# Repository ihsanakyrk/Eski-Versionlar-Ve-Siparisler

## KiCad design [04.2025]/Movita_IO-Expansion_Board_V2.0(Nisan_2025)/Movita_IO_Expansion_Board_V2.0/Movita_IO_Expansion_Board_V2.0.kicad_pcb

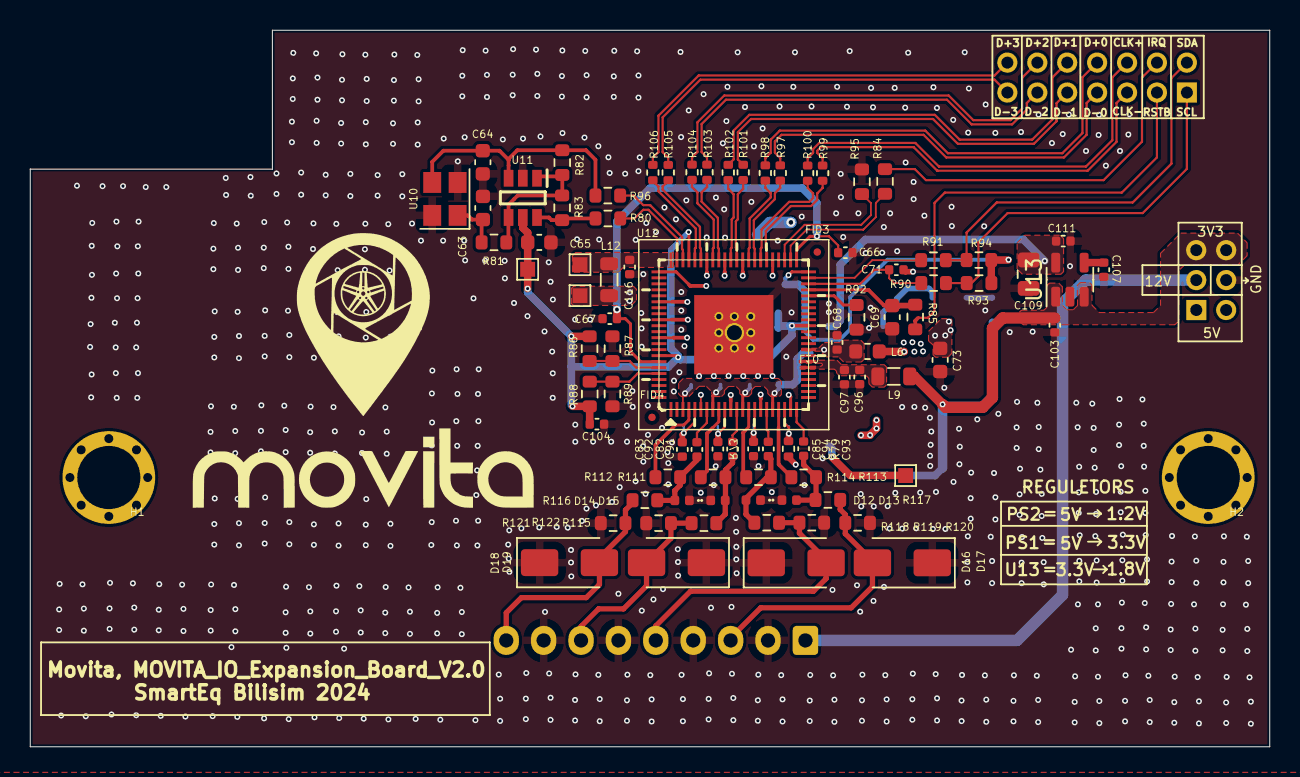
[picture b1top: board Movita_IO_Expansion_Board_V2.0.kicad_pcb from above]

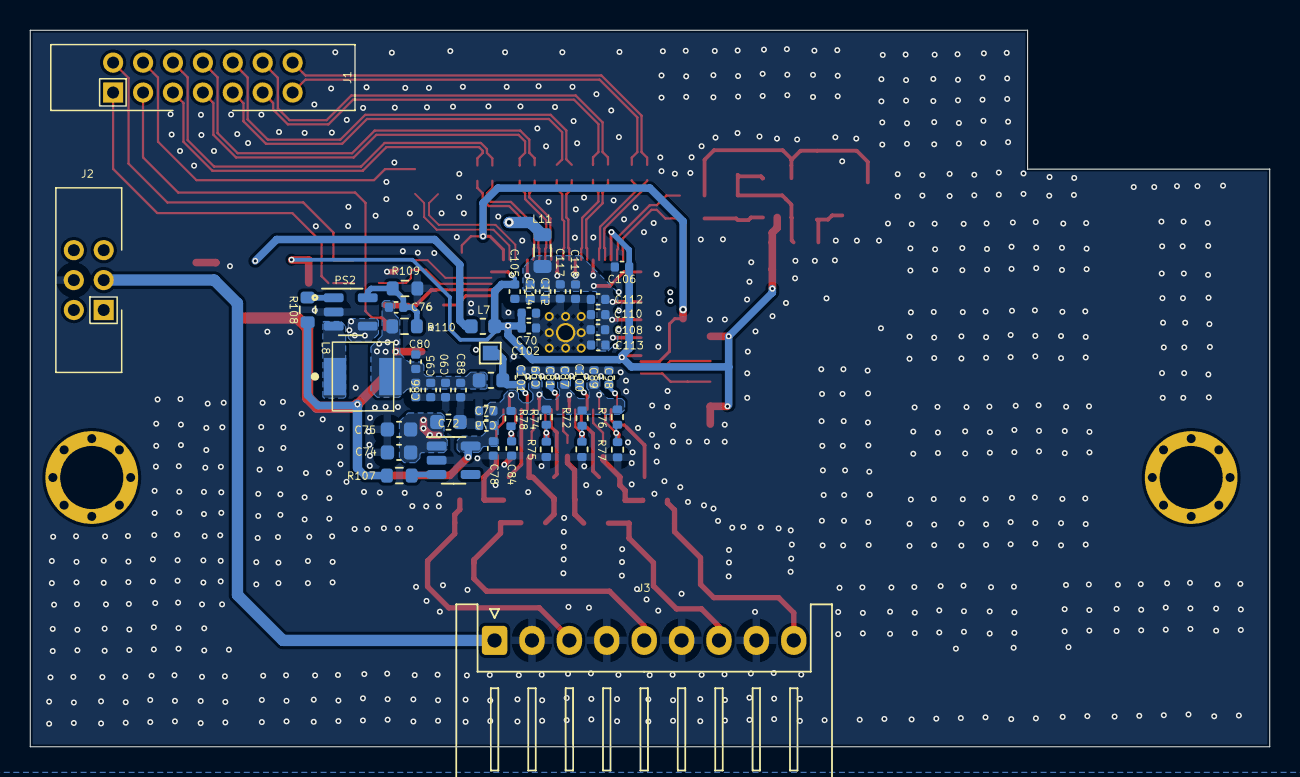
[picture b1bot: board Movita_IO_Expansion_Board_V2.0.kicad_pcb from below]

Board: 4 copper layers, 82.9 x 47.9 mm, 140 parts (53 on the bottom side), 76 nets.

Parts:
C63, C64: 8pF; C_0603_1608Metric
C65: 1uF; C_0603_1608Metric
C66, C67, C68, C70, C79, C81, C82, C83, C84, C85, C87, C89, C90, C91, C92, C93, C94, C95, C96, C98, C99, C100, C101, C102, C103, C104, C105, C106, C107, C108, C110, C111, C112, C113, C114, C115, C116, C117, C118: 100nF; C_0402_1005Metric
C69: 1nF; C_0603_1608Metric
C71: 56pF; C_0402_1005Metric
C72, C73: 10uF; C_0603_1608Metric
C74, C75: 100nF; C_0603_1608Metric
C76: 100pF; C_0402_1005Metric
C77, C80, C86: 10uF; C_0402_1005Metric
C78, C88, C97: 4.7uF; C_0402_1005Metric
C109: 10uF; C_0805_2012Metric
D12, D13, D14, D15: EZJ-Z0V800AA; D_0402_1005Metric
D16, D17, D18, D19: SMAJ30CA; D_SMA
FID3, FID4: Fiducial; Fiducial_0.5mm_Mask1mm
H1, H2: M3x*0.5 L=6; Screw Terminal Shinbo
J1: Conn_01x14_Pin; Analog signal connector
J2: Conn_01x06_Pin; Analog power connector
J3: :JST_XH_S9B-XH-A_1x09_P2.50mm_MALE_Horizontal; JST_XH_S9B-XH-A_1x09_P2.50mm_Horizontal
L6, L7: 742792651; L_0603_1608Metric
L8: YSPI0420-1R0M; HCM0420-1R0M
L9, L11, L12: YI201209U101-3R0T; L_0805_2012Metric
L10: CBW160808U101T; L_0603_1608Metric
PS1: RT9013-33GB; SOT-23-5
PS2: ETA3448S2F; SOT-23-5
R72, R74, R76, R78: 1M; R_0402_1005Metric
R73, R75, R77, R79: 510K; R_0402_1005Metric
R80, R81, R90, R91: 100R; R_0603_1608Metric
R82: 560K; R_0603_1608Metric
R83, R87, R89, R96: DNP; R_0603_1608Metric
R84, R85, R95: 0R; R_0603_1608Metric
R86, R88: 4.7K; R_0603_1608Metric
R92, R115, R116, R117, R118: 22R; R_0603_1608Metric
R93, R94: 2K; R_0603_1608Metric
R97, R98, R99, R100, R101, R102, R103, R104, R105, R106: 22R; R_0402_1005Metric
R107, R108: 10K; R_0603_1608Metric
R109, R110: 150K; R_0603_1608Metric
R111, R112, R113, R114: 47R; R_0603_1608Metric
R119, R120, R121, R122: 75R; R_0603_1608Metric
TP13, TP14, TP15, TP16, TP17: DNP; TestPoint_Pad_1.0x1.0mm
U10: CF4027M00010; Crystal_SMD_3225-4Pin_3.2x2.5mm
U11: NL27WZU04DTT1G
U12: TP2815; EPQFN_88L_10X10
U13: TP5108E23E-18; SOT-23-5

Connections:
/CSI_AHD/+3.3V: C103.1, J2.5, J2.6, L9.1, R107.1, R108.1, U13.1 (IN), U13.3 (EN)
/CSI_AHD/+5V: C72.1, C73.1, C74.1, C75.1, J2.1, J2.2, PS1.1 (VIN), PS2.4 (IN)
/CSI_AHD/CK1_N: R99.2, U12.50 (CKN_1)
/CSI_AHD/CK1_P: R100.2, U12.51 (CKP_1)
/CSI_AHD/D01_N: R97.2, U12.52 (D0N_1)
/CSI_AHD/D01_P: R98.2, U12.53 (D0P_1)
/CSI_AHD/D11_N: R101.2, U12.55 (D1N_1)
/CSI_AHD/D11_P: R102.2, U12.56 (D1P_1)
/CSI_AHD/D21_N: R103.2, U12.58 (D2N_1)
/CSI_AHD/D21_P: R104.2, U12.59 (D2P_1)
/CSI_AHD/D31_N: R105.2, U12.61 (D3N_1)
/CSI_AHD/D31_P: R106.2, U12.62 (D3P_1)
/CSI_AHD/DVDD: C66.2, C67.2, C68.2, L6.2, U12.31 (DVDD1), U12.45 (DVDD3), U12.82 (DVDD2)
/CSI_AHD/LX: L8.1, PS2.3 (LX)
/CSI_AHD/TP2855_CLK+: J1.6, R100.1
/CSI_AHD/TP2855_CLK-: J1.5, R99.1
/CSI_AHD/TP2855_D+0: J1.8, R98.1
/CSI_AHD/TP2855_D+1: J1.10, R102.1
/CSI_AHD/TP2855_D+2: J1.12, R104.1
/CSI_AHD/TP2855_D+3: J1.14, R106.1
/CSI_AHD/TP2855_D-0: J1.7, R97.1
/CSI_AHD/TP2855_D-1: J1.9, R101.1
/CSI_AHD/TP2855_D-2: J1.11, R103.1
/CSI_AHD/TP2855_D-3: J1.13, R105.1
/CSI_AHD/TP2855_IIC_ADDR0: R86.1, R87.2, U12.83 (SAD0)
/CSI_AHD/TP2855_IIC_ADDR1: R88.1, R89.2, U12.84 (SAD1)
/CSI_AHD/TP2855_IRQ: J1.4, R84.1
/CSI_AHD/TP2855_OSC_CLK_IN: R80.1, U12.65 (XTI)
/CSI_AHD/TP2855_OSC_CLK_OUT: R96.2, U12.64 (XTO)
/CSI_AHD/TP2855_PTZ1: R112.2, U12.4 (PTZ1)
/CSI_AHD/TP2855_PTZ2: R111.2, U12.9 (PTZ2)
/CSI_AHD/TP2855_PTZ3: R114.2, U12.14 (PTZ3)
/CSI_AHD/TP2855_PTZ4: R113.2, U12.19 (PTZ4)
/CSI_AHD/TP2855_RSTB: J1.3, R85.1
/CSI_AHD/TP2855_SCL: J1.1, R90.1, R93.2
/CSI_AHD/TP2855_SDA: J1.2, R91.1, R94.2
/CSI_AHD/TP2855_TEST_MODE: R95.2, U12.47 (TEST)
/CSI_AHD/TP2855_VIN1N: C83.1, R76.1, R77.2, U12.5 (VIN1N)
/CSI_AHD/TP2855_VIN1P: C92.1, U12.7 (VIN1)
/CSI_AHD/TP2855_VIN2N: C82.1, R72.1, R73.2, U12.10 (VIN2N)
/CSI_AHD/TP2855_VIN2P: C91.1, U12.12 (VIN2)
/CSI_AHD/TP2855_VIN3N: C85.1, R74.1, R75.2, U12.15 (VIN3N)
/CSI_AHD/TP2855_VIN3P: C94.1, U12.17 (VIN3)
/CSI_AHD/TP2855_VIN4N: C84.1, R78.1, R79.2, U12.20 (VIN4N)
/CSI_AHD/TP2855_VIN4P: C93.1, U12.22 (VIN4)
/CSI_AHD/TP2855_XOUT: C64.2, R82.2, R96.1, U10.3 (XOUT), U11.3 (INA2)
/CSI_AHD/VBUS: J2.3, J3.1
Earth: C63.1, C64.1, C65.2, C66.1, C67.1, C68.1, C69.1, C70.2, C71.1, C72.2, C73.2, C74.2, C75.2, C77.2, C78.2, C79.2, C80.2, C81.2, C82.2, C83.2, C84.2, C85.2, C86.2, C87.2, C88.2, C89.2, C90.2, C95.2, C96.2, C97.2, C98.2, C99.2, C100.2, C101.2, C102.2, C103.2, C104.2, C105.2, C106.2, C107.2, C108.2, C109.2, C110.2, C111.2, C112.2, C113.2, C114.2, C115.2, C116.2, C117.2, C118.2, D12.1 (A1), D13.1 (A1), D14.1 (A1), D15.1 (A1), D16.1 (A1), D17.1 (A1), D18.1 (A1), D19.1 (A1), J2.4, J3.2, J3.4, J3.6, J3.8, PS1.2 (GND), PS2.2 (GND), R73.1, R75.1, R77.1, R79.1, R87.1, R89.1, R92.1, R95.1, R109.1, R119.2, R120.2, R121.2, R122.2, U10.2 (GND2), U10.4 (GND1), U11.2 (GND), U12.89 (EPAD), U13.2 (GND)
unnamed: C94.2, D12.2 (A2), R114.1, R118.2
unnamed: C93.2, D13.2 (A2), R113.1, R117.2
unnamed: C92.2, D14.2 (A2), R112.1, R116.2
unnamed: C91.2, D15.2 (A2), R111.1, R115.2
unnamed: D16.2 (A2), J3.5, R118.1, R119.1
unnamed: D17.2 (A2), J3.3, R117.1, R120.1
unnamed: D18.2 (A2), J3.9, R116.1, R121.1
unnamed: D19.2 (A2), J3.7, R115.1, R122.1
unnamed: PS1.3 (EN), R107.2
unnamed: PS2.1 (EN), R108.2
unnamed: C76.2, PS2.5 (OUT), R109.2, R110.1
unnamed: C63.2, R81.1, U10.1 (XIN)
unnamed: R81.2, R82.1, R83.2, U11.1 (INA1), U11.4 (OUT*Y2)
unnamed: R80.2, R83.1, U11.6 (OUT*Y1)
unnamed: R92.2, U12.40 (ALINKI)
unnamed: R84.2, U12.46 (IRQ)
unnamed: C69.2, R85.2, U12.41 (RSTB)
unnamed: C71.2, R90.2, U12.42 (SCL)
unnamed: R91.2, U12.43 (SDA)
unnamed: C107.1, U13.4 (BP)
TP2855_AVDD1V2: C98.1, C99.1, C100.1, C101.1, L10.2, TP15.1, U12.3 (AVDD1_1), U12.8 (AVDD1_2), U12.13 (AVDD1_3), U12.18 (AVDD1_4)
TP2855_AVDD3V3: C77.1, C78.1, C79.1, C81.1, C87.1, C89.1, PS1.5 (VOUT), R72.2, R74.2, R76.2, R78.2, TP13.1, U12.6 (AVDD3_1), U12.11 (AVDD3_2), U12.16 (AVDD3_3), U12.21 (AVDD3_4)
TP2855_AVDDPLL_1V2: C116.1, L12.2, TP17.1, U12.66 (VDDPPL)
TP2855_CODEC_V3V3: C96.1, C97.1, L9.2, U12.28 (AADVDD), U12.29 (ADAVDD)
TP2855_DVDD1V2: C108.1, C110.1, C112.1, C113.1, C114.1, C115.1, C117.1, C118.1, L11.2, U12.49 (VDDM2_1), U12.54 (VDDM1_1), U12.57 (VDDM3_1), U12.60 (VDDM4_1), U12.67 (VDDM1_2), U12.72 (VDDM4_2), U12.75 (VDDM2_2), U12.78 (VDDM3_2)
TP2855_VCCIO: C65.1, C70.1, C102.1, C104.1, C105.1, C106.1, L7.2, R86.2, R88.2, R93.1, R94.1, TP16.1, U11.5 (VCC), U12.35 (VDD_IO3), U12.44 (VDD_IO1), U12.63 (VDD_IO2), U12.81 (VDD_IO4)
VDDIO_18: C109.1, C111.1, L7.1, U13.5 (OUT)
VDD_1V2: C76.1, C80.1, C86.1, C88.1, C90.1, C95.1, L6.1, L8.2, L10.1, L11.1, L12.1, R110.2, TP14.1

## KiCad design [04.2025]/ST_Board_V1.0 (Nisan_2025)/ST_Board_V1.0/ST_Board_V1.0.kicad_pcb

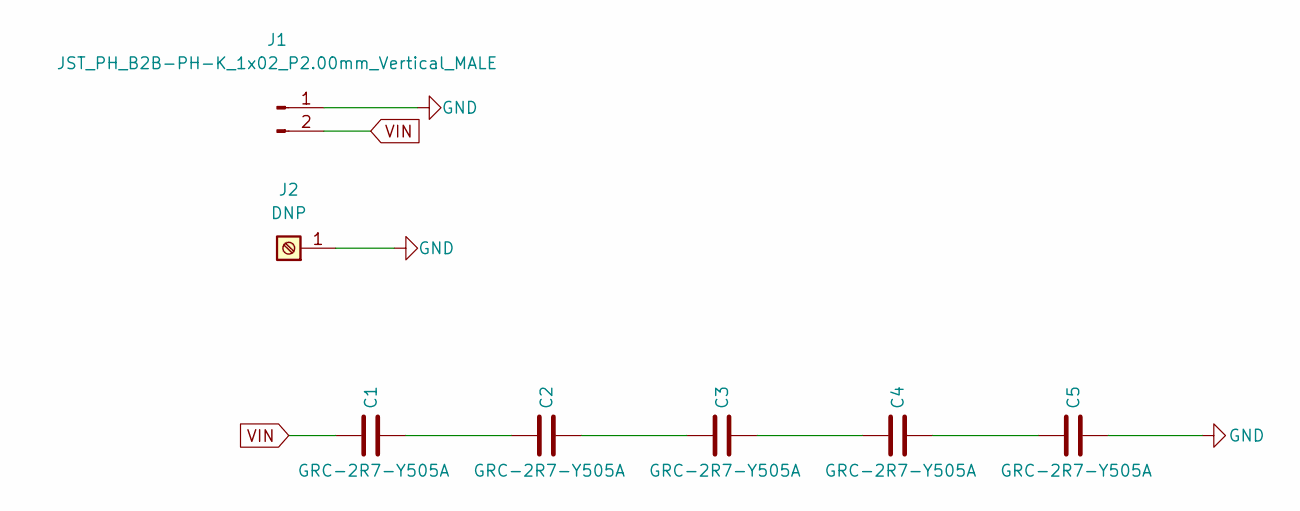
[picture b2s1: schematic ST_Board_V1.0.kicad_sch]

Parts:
C1, C2, C3, C4, C5: GRC-2R7-Y505A
J1: JST_PH_B2B-PH-K_1x02_P2.00mm_Vertical_MALE; JST_PH_B2B-PH-K_1x02_P2.00mm_Vertical
J2: DNP; Screw Terminal Shinbo

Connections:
GND: C5.2, J1.1, J2.1
unnamed: C1.2, C2.1
unnamed: C2.2, C3.1
unnamed: C3.2, C4.1
unnamed: C4.2, C5.1
VIN: C1.1, J1.2

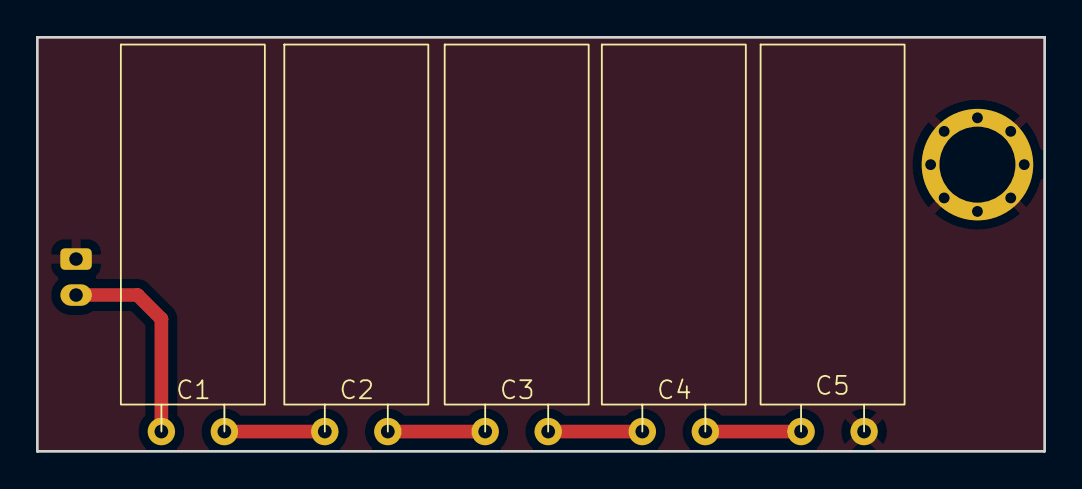
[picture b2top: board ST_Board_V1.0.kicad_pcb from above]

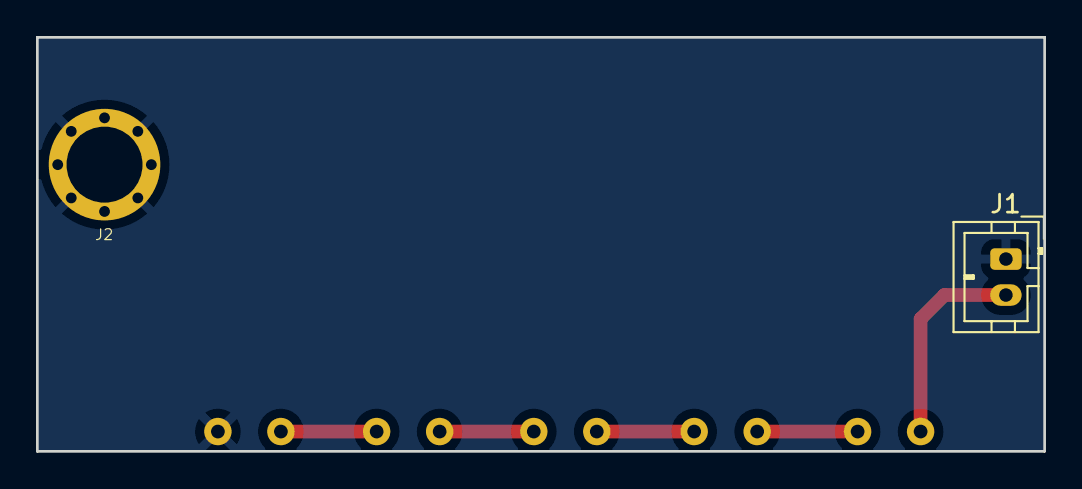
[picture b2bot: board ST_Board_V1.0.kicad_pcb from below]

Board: 2 copper layers, 56.0 x 23.0 mm, 7 parts (2 on the bottom side), 6 nets.

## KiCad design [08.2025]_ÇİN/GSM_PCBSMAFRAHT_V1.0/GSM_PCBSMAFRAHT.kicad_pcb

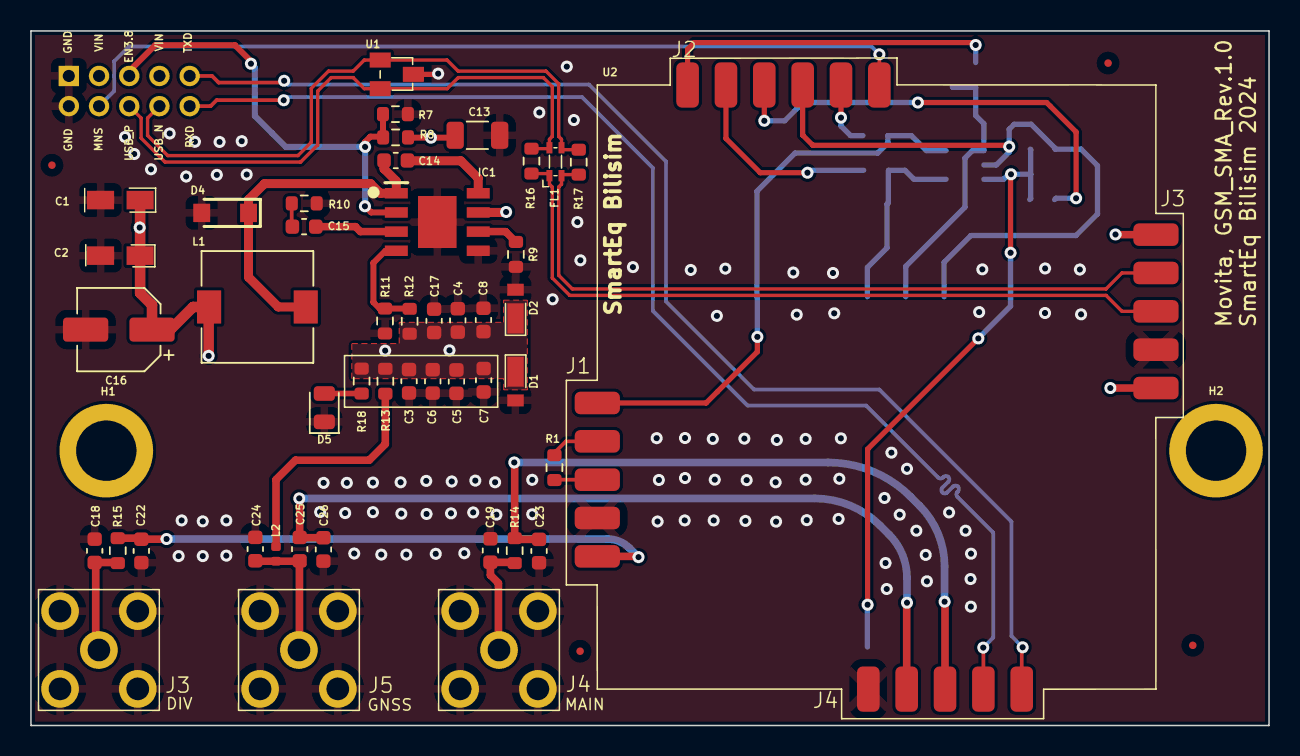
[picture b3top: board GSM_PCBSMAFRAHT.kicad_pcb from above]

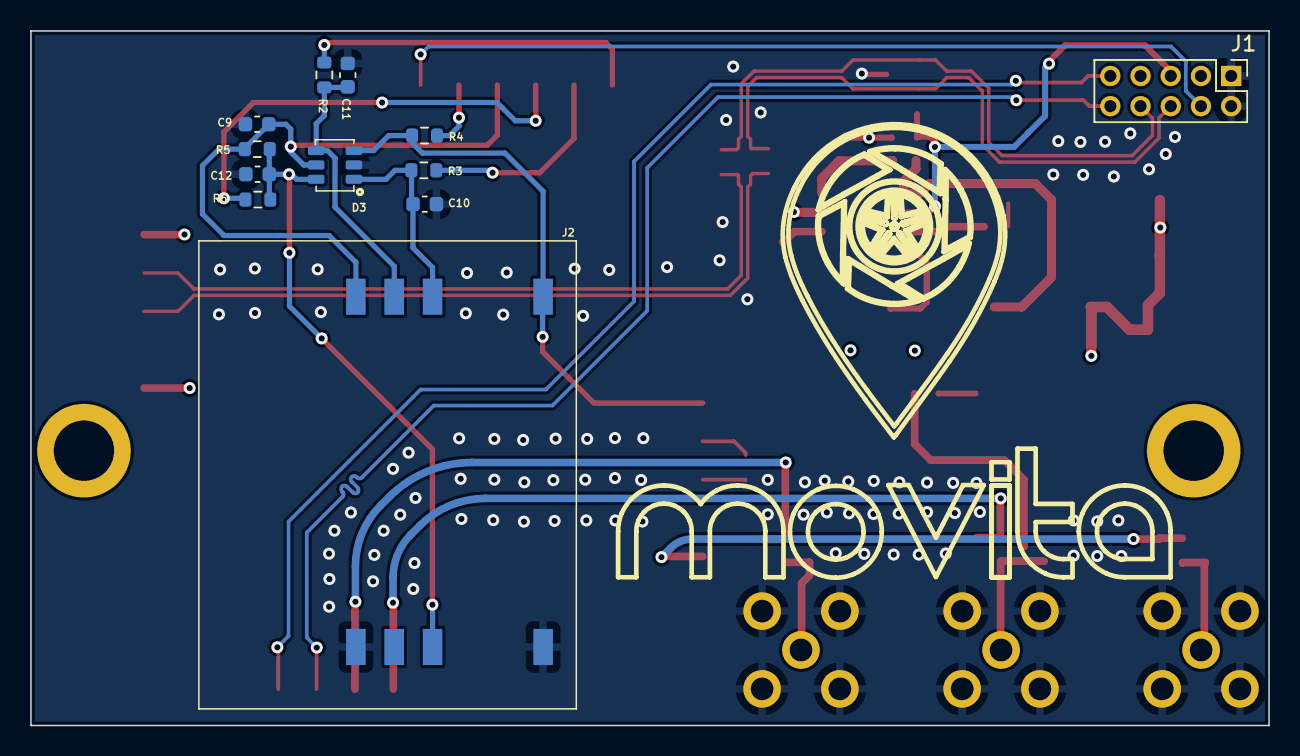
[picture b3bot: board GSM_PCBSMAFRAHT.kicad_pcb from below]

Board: 4 copper layers, 82.0 x 46.0 mm, 64 parts (12 on the bottom side), 36 nets.

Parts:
C1, C2: T490A107M006ATE500; T490A
C3, C4, C10, C11, C12: 33pF; C_0603_1608Metric
C5, C6: 10pF; C_0603_1608Metric
C7, C8, C9, C17: 0.1uF; C_0603_1608Metric
C13: 10uF; C_1206_3216Metric
C14: 100nF; C_0603_1608Metric
C15: 220pF; C_0603_1608Metric
C16: 100uF; CP_Elec_5x5.4
C18, C19, C22, C23, C24, C26: DNP; C_0603_1608Metric
C25: 100pF; C_0603_1608Metric
D1, D2: TDZVTR5.1
D3: ESDA6V1-5SC6
D4: SS34FA; SS4FA
D5: RED LED; LED_0805_2012Metric
FID1, FID2, FID3, FID4: Fiducial; Fiducial_0.5mm_Mask1.5mm
FL1: ACM2012-900-2P-T002
H1, H2: DNP; Screw_Terminal_1x1
IC1: MP1584EN-LF-Z
J1: FEMALE Through Hole Pin Header; PinHeader_2x05_P2.00mm_Vertical
J2: 91228-3002; 912283002
J3, J4, J5: PCB.SMAFRA.HT
L1: 10uH; L_7.3x7.3_H3.5
L2: 47nH 5%; L_0402_1005Metric
R1, R14, R15: 0R; R_0603_1608Metric
R2, R3, R6: 22R; R_0603_1608Metric
R4: 51K; R_0603_1608Metric
R5: 15K; R_0603_1608Metric
R7: 24.9K; R_0603_1608Metric
R8: 100K; R_0603_1608Metric
R9: 200K; R_0603_1608Metric
R10: 68.1K; R_0603_1608Metric
R11: 40.2K; R_0603_1608Metric
R12: 150K; R_0603_1608Metric
R13: 10R; R_0603_1608Metric
R16, R17: DNP; R_0603_1608Metric
R18: 1K; R_0603_1608Metric
U1: TPET05US3
U2: DNP; GSM_Castelled

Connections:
/91228-3002/EN3V8: IC1.2 (EN), J1.5, R7.1, R8.2
/91228-3002/MODEM_NET_STATUS: J1.4, U2.16 (MODEM+NET+STATUS)
/91228-3002/RXD: J1.10, U2.2 (RXD)
/91228-3002/TXD: J1.9, U2.1 (TXD)
/91228-3002/USB_GSM_N: FL1.3, J1.8, R17.1, U1.1
/91228-3002/USB_GSM_P: FL1.4, J1.6, R16.2, U1.2
/91228-3002/USIM_CLK: R3.1, U2.12 (USIM_CLK)
/91228-3002/USIM_DATA: R6.1, U2.13 (USIM_DATA)
/91228-3002/USIM_PRESENCE: D3.3, J2.8 (PRESENCE), R4.1, U2.10 (USIM_PRESENCE)
/91228-3002/USIM_RST: R2.1, U2.11 (USIM_RST)
/91228-3002/USIM_VDD: C9.1, D3.5, J2.6 (VCC), R5.1, U2.14 (USIM_VDD)
/91228-3002/VDD_EXT_1V8: R4.2, U2.15 (VDD_EXT_1V8)
/91228-3002/VIN: C13.1, IC1.7 (VIN), J1.3, J1.7, R8.1
/GSM_Castelled/+3V8: C1.1, C2.1, C3.1, C4.1, C5.1, C6.1, C7.1, C8.1, C16.1, C17.1, D1.1 (K), D2.1 (K), L1.2, R12.2, R13.1, R18.2, U2.17 (+3V8), U2.21 (+3V8)
/GSM_Castelled/ANT_DIV: C22.1, R15.2, U2.6 (ANT_DIV)
/GSM_Castelled/ANT_GNSS: C25.2, C26.1, U2.4 (ANT_GNSS)
/GSM_Castelled/ANT_MAIN: C23.1, R14.2, U2.3 (ANT_MAIN)
/GSM_Castelled/USB_N: FL1.2, R17.2, U2.18 (USB_N)
/GSM_Castelled/USB_P: FL1.1, R16.1, U2.19 (USB_P)
GND: C1.2, C2.2, C3.2, C4.2, C5.2, C6.2, C7.2, C8.2, C9.2, C10.2, C11.2, C12.2, C13.2, C16.2, C17.2, C18.1, C19.1, C22.2, C23.2, C24.1, C26.2, D1.2 (A), D2.2 (A), D3.2, D4.2 (A), D5.1 (K), IC1.5 (GND), IC1.9 (EP), J1.1, J1.2, J2.1 (GND), J2.7 (NC), J3.2, J3.3, J3.4, J3.5, J4.2, J4.3, J4.4, J4.5, J5.2, J5.3, J5.4, J5.5, R7.2, R9.2, R10.2, R11.2, U1.3, U2.5 (GND), U2.7 (GND), U2.20 (GND)
unnamed: C15.2, R10.1
unnamed: C14.2, D4.1 (K), IC1.1 (SW), L1.1
unnamed: D5.2 (A), R18.1
unnamed: C14.1, IC1.8 (BST)
unnamed: C15.1, IC1.3 (COMP)
unnamed: IC1.4 (FB), R11.1, R12.1
unnamed: IC1.6 (FREQ), R9.1
unnamed: C10.1, D3.1, J2.4 (CLK), R3.2
unnamed: C12.1, D3.6, J2.3 (I/O), R5.2, R6.2
unnamed: C11.1, D3.4, J2.5 (RST), R2.2
unnamed: C18.2, J3.1, R15.1
unnamed: C19.2, J4.1, R14.1
unnamed: C24.2, C25.1, J5.1, L2.2
unnamed: L2.1, R13.2
unnamed: R1.1, U2.8 (CTS)
unnamed: R1.2, U2.9 (RTS)

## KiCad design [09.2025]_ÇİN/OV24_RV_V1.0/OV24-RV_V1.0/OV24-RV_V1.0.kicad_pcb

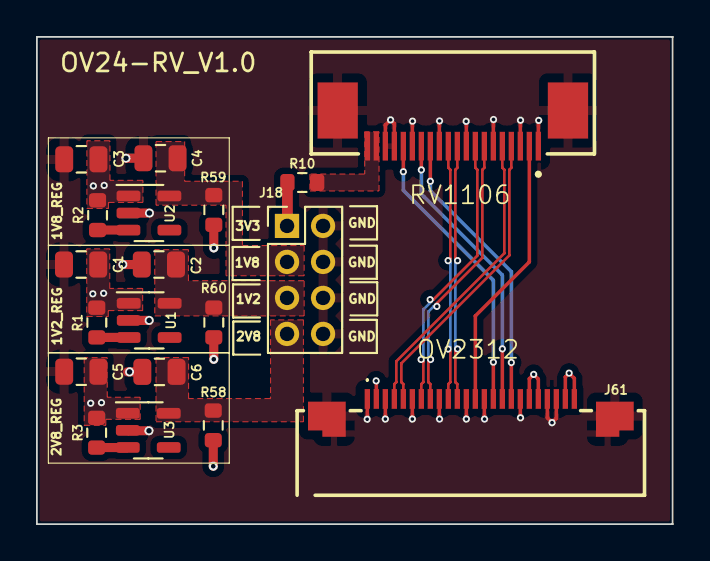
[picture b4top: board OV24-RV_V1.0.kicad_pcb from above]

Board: 2 copper layers, 35.3 x 27.1 mm, 19 parts (0 on the bottom side), 22 nets.

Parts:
C1, C2, C3, C4, C5, C6: 10uF; C_0805_2012Metric
J18: DNP; PinHeader_2x04_P2.00mm_Vertical
J39: FFC SOCKET DR_TOP 0.5MM -20P; SAMTEC_ZF5S-20-02-T-WT
J61: FFC SOCKET DR_BOTTOM 0.5MM -24P; F32R1A7H111024
R1, R2, R3: 5K; R_0603_1608Metric
R10, R58, R59, R60: 0R; R_0603_1608Metric
U1: RT9080-12GJ5; SOT-23-5
U2: RT9080-18GJ5; SOT-23-5
U3: RT9080-28GJ5; SOT-23-5

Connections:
/+3V3: J39.19, J39.20, R10.2
/MIPI_I2C_SCL: J39.13, J61.17
/MIPI_I2C_SDA: J39.14, J61.16
/MIPI_LVDS_CLK_N: J39.08 (Pin_8), J61.7
/MIPI_LVDS_CLK_P: J39.07 (Pin_7), J61.8
/MIPI_LVDS_D0_N: J39.05 (Pin_5), J61.4
/MIPI_LVDS_D0_P: J39.04 (Pin_4), J61.5
/MIPI_LVDS_D1_N: J39.11, J61.10
/MIPI_LVDS_D1_P: J39.10, J61.11
/MIPI_LVDS_MCLK0: J39.02 (Pin_2), J61.13
/MIPI_LVDS_RST: J39.16, J61.15
AVDD2V8: C6.1, J18.7, R58.1, U3.5 (OUT)
DOVDD1V8: C4.1, J18.3, R59.1, U2.5 (OUT)
DVDD1V2: C2.1, J18.5, R60.1, U1.5 (OUT)
GND: C1.2, C2.2, C3.2, C4.2, C5.2, C6.2, J18.2, J18.4, J18.6, J18.8, J39.01 (Pin_1), J39.03 (Pin_3), J39.06 (Pin_6), J39.09 (Pin_9), J39.12, J39.15, J39.17, J39.18, J39.S1 (Pin_22), J39.S2 (Pin_21), J61.1, J61.3, J61.6, J61.9, J61.12, J61.14, J61.18, J61.21, J61.22, J61.25, J61.26, U1.2 (GND), U2.2 (GND), U3.2 (GND)
unnamed: J61.2, R59.2
unnamed: J61.19, J61.20, R60.2
unnamed: J61.23, J61.24, R58.2
unnamed: R1.2, U1.3 (EN)
unnamed: R2.2, U2.3 (EN)
unnamed: R3.2, U3.3 (EN)
VCC_3V3: C1.1, C3.1, C5.1, J18.1, R1.1, R2.1, R3.1, R10.1, U1.1 (IN), U2.1 (IN), U3.1 (IN)

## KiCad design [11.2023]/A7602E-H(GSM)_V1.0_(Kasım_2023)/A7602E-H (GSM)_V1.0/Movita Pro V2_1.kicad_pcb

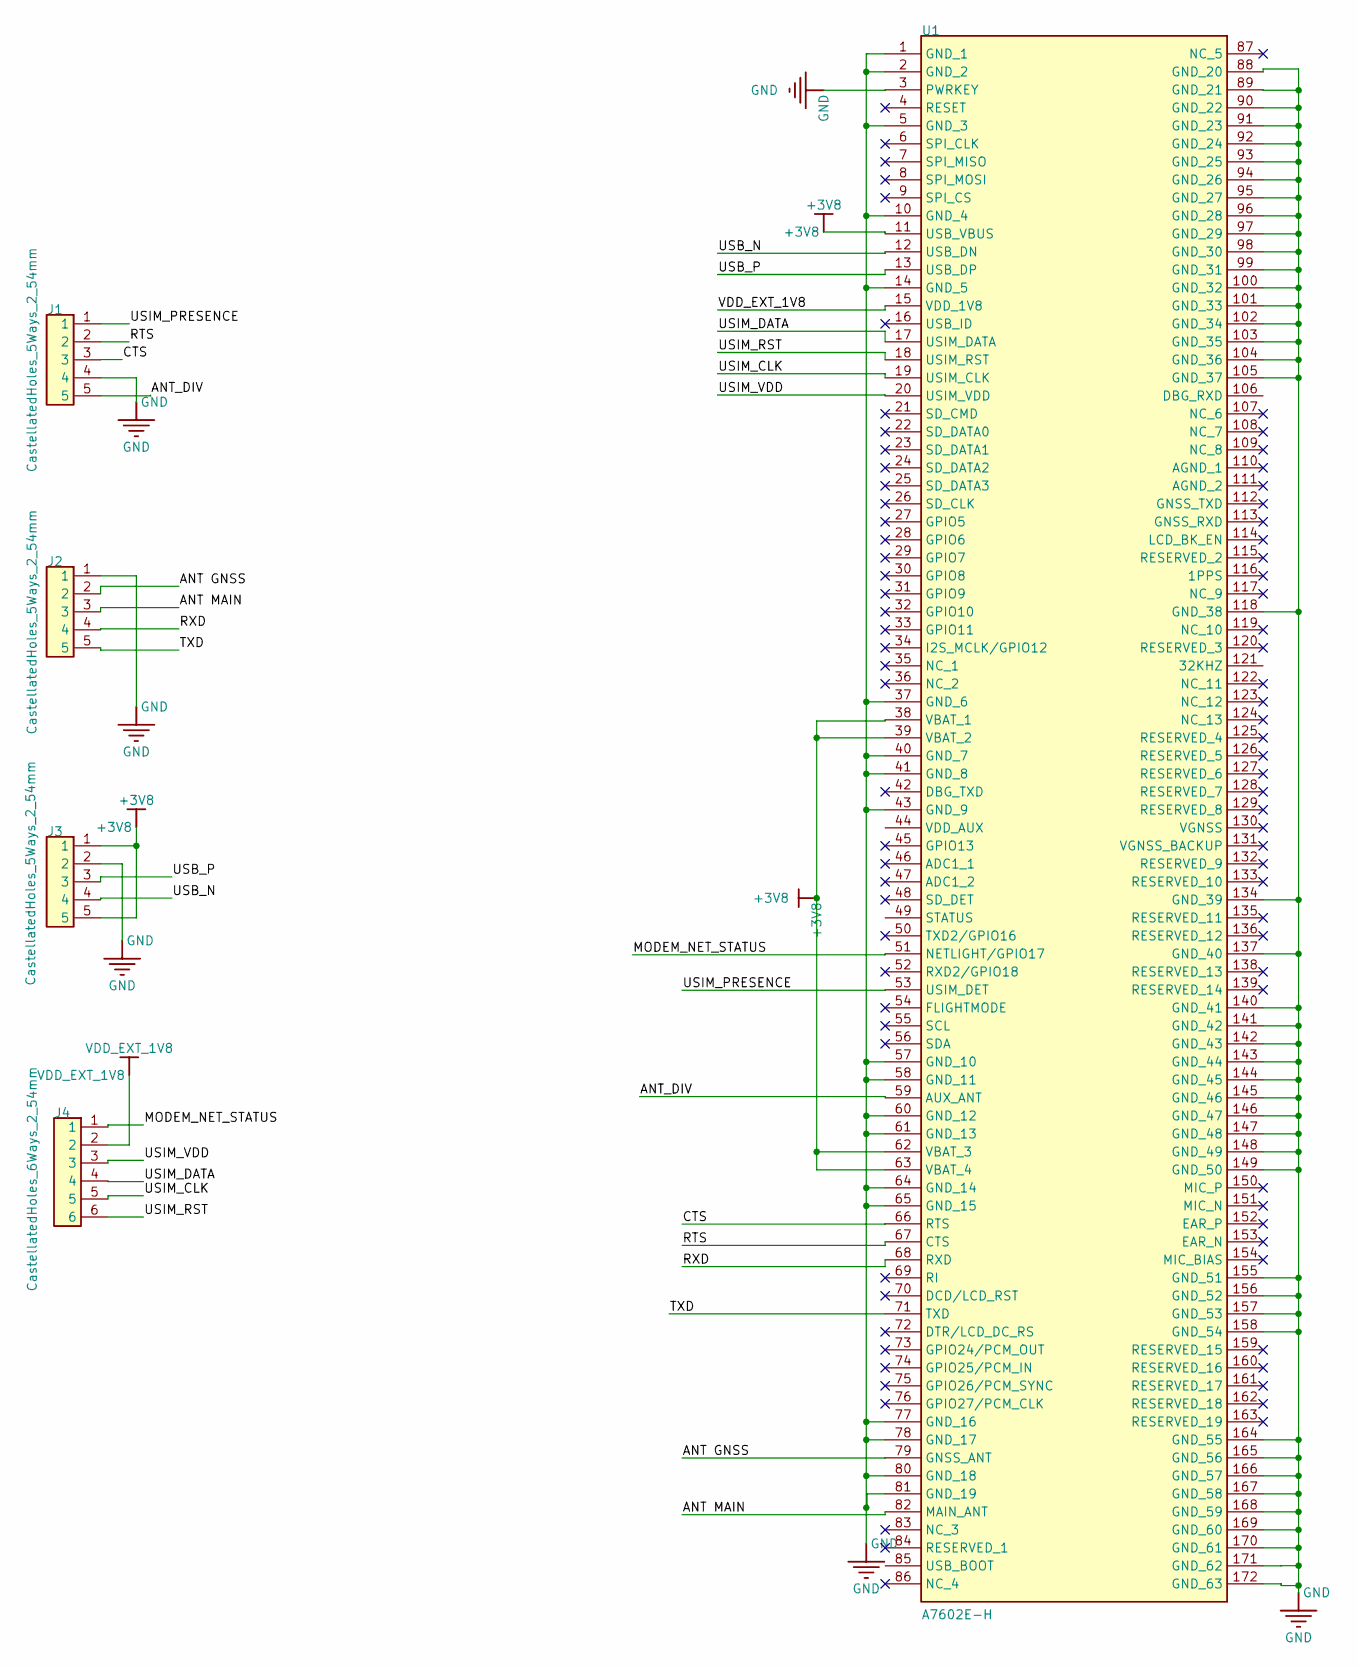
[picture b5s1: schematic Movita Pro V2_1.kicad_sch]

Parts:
J1, J2, J3: CastellatedHoles_5Ways_2_54mm; Castelled Pin Header 1x5 Ways 2.54
J4: CastellatedHoles_6Ways_2_54mm; Castelled Pin Header 1x6 Ways 2.54
U1: A7602E-H; A7602EH; MANUFACTURER_PART_NUMBER A7602E-H; MOUSER PART NUMBER *

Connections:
+3V8: J3.1, J3.5, U1.11 (USB_VBUS), U1.38 (VBAT_1), U1.39 (VBAT_2), U1.62 (VBAT_3), U1.63 (VBAT_4)
/ANT GNSS: J2.2, U1.79 (GNSS_ANT)
/ANT MAIN: J2.3, U1.82 (MAIN_ANT)
/ANT_DIV: J1.5, U1.59 (AUX_ANT)
/CTS: J1.3, U1.66 (RTS)
/MODEM_NET_STATUS: J4.1, U1.51 (NETLIGHT/GPIO17)
/RTS: J1.2, U1.67 (CTS)
/RXD: J2.4, U1.68 (RXD)
/TXD: J2.5, U1.71 (TXD)
/USB_N: J3.4, U1.12 (USB_DN)
/USB_P: J3.3, U1.13 (USB_DP)
/USIM_CLK: J4.5, U1.19 (USIM_CLK)
/USIM_DATA: J4.4, U1.17 (USIM_DATA)
/USIM_PRESENCE: J1.1, U1.53 (USIM_DET)
/USIM_RST: J4.6, U1.18 (USIM_RST)
/USIM_VDD: J4.3, U1.20 (USIM_VDD)
GND: J1.4, J2.1, J3.2, U1.1 (GND_1), U1.2 (GND_2), U1.3 (PWRKEY), U1.5 (GND_3), U1.10 (GND_4), U1.14 (GND_5), U1.37 (GND_6), U1.40 (GND_7), U1.41 (GND_8), U1.43 (GND_9), U1.57 (GND_10), U1.58 (GND_11), U1.60 (GND_12), U1.61 (GND_13), U1.64 (GND_14), U1.65 (GND_15), U1.77 (GND_16), U1.78 (GND_17), U1.80 (GND_18), U1.81 (GND_19), U1.88 (GND_20), U1.89 (GND_21), U1.90 (GND_22), U1.91 (GND_23), U1.92 (GND_24), U1.93 (GND_25), U1.94 (GND_26), U1.95 (GND_27), U1.96 (GND_28), U1.97 (GND_29), U1.98 (GND_30), U1.99 (GND_31), U1.100 (GND_32), U1.101 (GND_33), U1.102 (GND_34), U1.103 (GND_35), U1.104 (GND_36), U1.105 (GND_37), U1.118 (GND_38), U1.134 (GND_39), U1.137 (GND_40), U1.140 (GND_41), U1.141 (GND_42), U1.142 (GND_43), U1.143 (GND_44), U1.144 (GND_45), U1.145 (GND_46), U1.146 (GND_47), U1.147 (GND_48), U1.148 (GND_49), U1.149 (GND_50), U1.155 (GND_51), U1.156 (GND_52), U1.157 (GND_53), U1.158 (GND_54), U1.164 (GND_55), U1.165 (GND_56), U1.166 (GND_57), U1.167 (GND_58), U1.168 (GND_59), U1.169 (GND_60), U1.170 (GND_61), U1.171 (GND_62), U1.172 (GND_63)
VDD_EXT_1V8: J4.2, U1.15 (VDD_1V8)

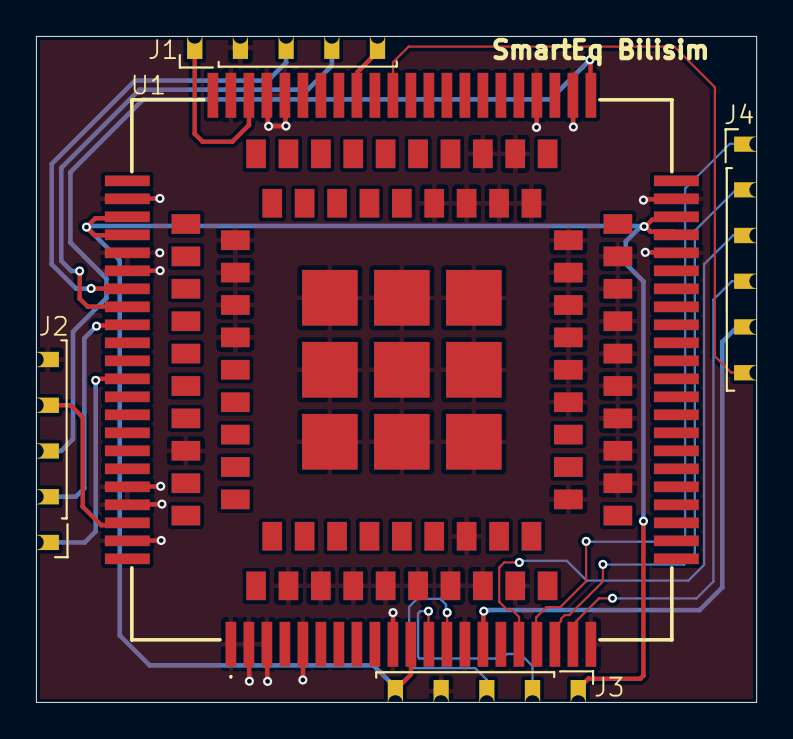
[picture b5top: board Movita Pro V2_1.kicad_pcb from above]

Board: 2 copper layers, 40.0 x 37.0 mm, 5 parts (0 on the bottom side), 18 nets.

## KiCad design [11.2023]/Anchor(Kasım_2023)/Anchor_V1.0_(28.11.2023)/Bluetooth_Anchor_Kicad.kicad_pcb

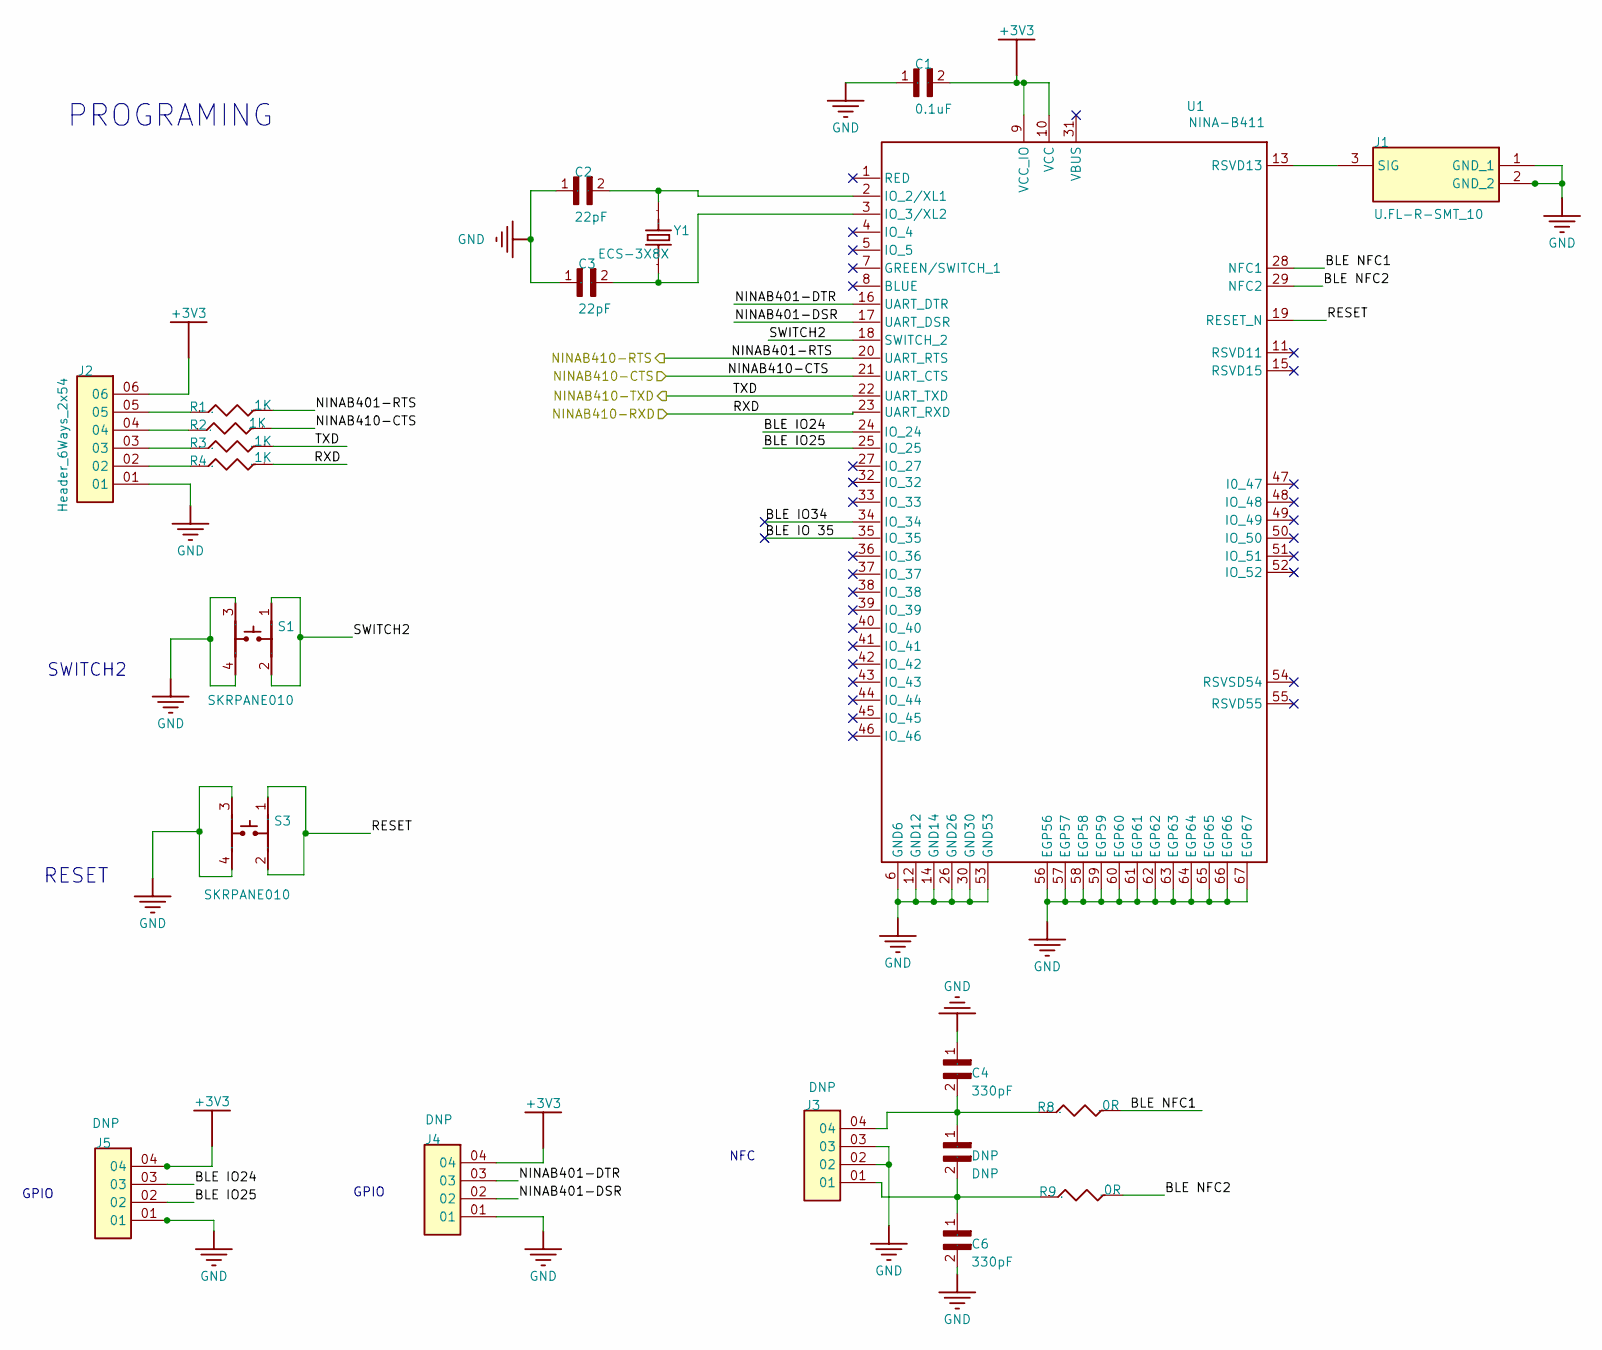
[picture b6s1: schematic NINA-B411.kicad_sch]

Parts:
C1: 0.1uF; C_0402
C2, C3: 22pF; C_0402
C4, C6: 330pF; C_0402
DNP: DNP; C_0402
J1: U.FL-R-SMT_10; UFLRSMT10; MANUFACTURER_PART_NUMBER U.FL-R-SMT(10); MOUSER PART NUMBER 798-U.FL-R-SMT10
J2: Header_6Ways_2x54
J3, J4, J5: DNP; Header_4Ways_2x54_Male
R1, R2, R3, R4: 1K; Res_0402
R8, R9: 0R; Res_0402
S1, S3: SKRPANE010
U1: NINA-B411; NINA_LGA67R_1160X1000X223_PIN - duplicate
Y1: ECS-3X8X; XTAL_ECS-3X8X

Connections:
+3V3: C1.2, J2.06, J4.04, J5.04, U1.9 (VCC_IO), U1.10 (VCC); also elsewhere on the board
BLE IO24: J5.03, U1.24 (IO_24)
BLE IO25: J5.02, U1.25 (IO_25)
BLE IO34: U1.34 (IO_34)
BLE IO 35: U1.35 (IO_35)
BLE NFC1: R8.2, U1.28 (NFC1)
BLE NFC2: R9.2, U1.29 (NFC2)
GND: C1.1, C2.1, C3.1, C4.1, C6.2, J1.1 (GND_1), J1.2 (GND_2), J2.01, J3.02, J3.03, J4.01, J5.01, S1.3, S1.4, S3.3, S3.4, U1.6 (GND6), U1.12 (GND12), U1.14 (GND14), U1.26 (GND26), U1.30 (GND30), U1.53 (GND53), U1.56 (EGP56), U1.57 (EGP57), U1.58 (EGP58), U1.59 (EGP59), U1.60 (EGP60), U1.61 (EGP61), U1.62 (EGP62), U1.63 (EGP63), U1.64 (EGP64), U1.65 (EGP65), U1.66 (EGP66), U1.67 (EGP67); also elsewhere on the board
NINAB401-DSR: J4.02, U1.17 (UART_DSR)
NINAB401-DTR: J4.03, U1.16 (UART_DTR)
NINAB401-RTS: R1.2, U1.20 (UART_RTS); also elsewhere on the board
NINAB410-CTS: R2.2, U1.21 (UART_CTS); also elsewhere on the board
NetC2_2: C2.2, U1.2 (IO_2/XL1), Y1.2
NetC3_2: C3.2, U1.3 (IO_3/XL2), Y1.1
NetC4_2: C4.2, J3.04, R8.1; also elsewhere on the board
NetC6_1: C6.1, J3.01, R9.1; also elsewhere on the board
NetJ1_3: J1.3 (SIG), U1.13 (RSVD13)
NetJ2_02: J2.02, R4.1
NetJ2_03: J2.03, R3.1
NetJ2_04: J2.04, R2.1
NetJ2_05: J2.05, R1.1
RESET: S3.1, S3.2, U1.19 (RESET_N)
RXD: R4.2, U1.23 (UART_RXD); also elsewhere on the board
SWITCH2: S1.1, S1.2, U1.18 (SWITCH_2)
TXD: R3.2, U1.22 (UART_TXD); also elsewhere on the board

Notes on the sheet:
NFC
SWITCH2
GPIO
PROGRAMING
RESET
